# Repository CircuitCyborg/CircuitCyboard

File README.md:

# CircuitCyboard
A repo for my 153% Split Keyboard Design

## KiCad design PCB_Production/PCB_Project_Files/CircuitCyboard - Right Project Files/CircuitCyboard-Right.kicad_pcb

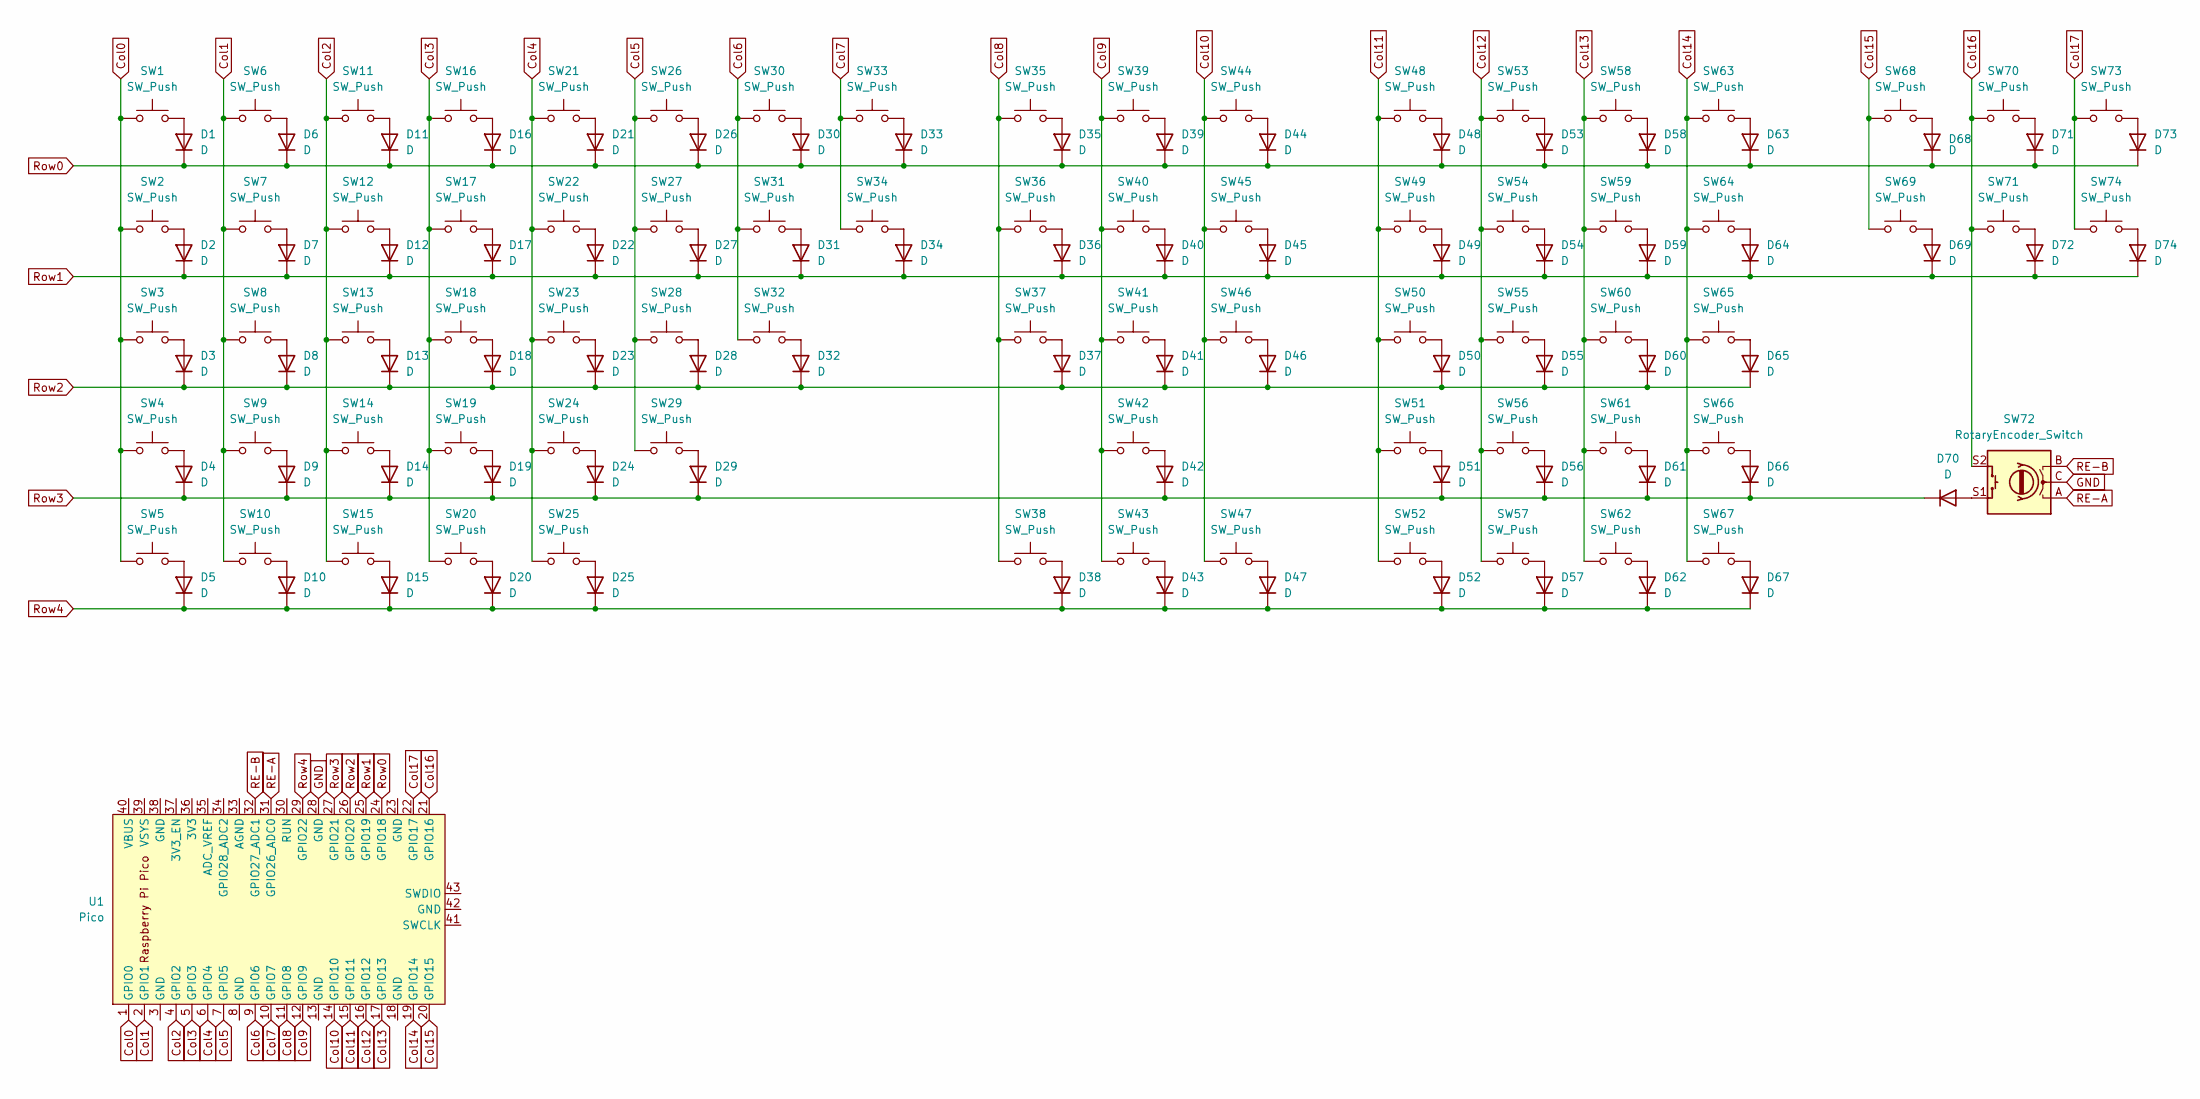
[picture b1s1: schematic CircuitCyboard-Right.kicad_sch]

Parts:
D1, D2, D3, D4, D5, D6, D7, D8, D9, D10, D11, D12, D13, D14, D15, D16, D17, D18, D19, D20, D21, D22, D23, D24, D25, D26, D27, D28, D29, D30, D31, D32, D33, D34, D35, D36, D37, D38, D39, D40, D41, D42, D43, D44, D45, D46, D47, D48, D49, D50, D51, D52, D53, D54, D55, D56, D57, D58, D59, D60, D61, D62, D63, D64, D65, D66, D67, D68, D69, D70, D71, D72, D73, D74: D; D_DO-35_SOD27_P12.70mm_Horizontal
SW1, SW2, SW3, SW4, SW6, SW7, SW8, SW9, SW10, SW11, SW12, SW13, SW14, SW15, SW16, SW17, SW18, SW19, SW20, SW21, SW22, SW23, SW24, SW25, SW26, SW27, SW28, SW30, SW31, SW34, SW35, SW36, SW37, SW38, SW39, SW40, SW41, SW42, SW43, SW44, SW45, SW46, SW47, SW48, SW49, SW50, SW51, SW52, SW53, SW54, SW55, SW56, SW57, SW58, SW59, SW60, SW61, SW62, SW63, SW64, SW65, SW66, SW67, SW68, SW69, SW70, SW71, SW73, SW74: SW_Push; SW_Cherry_MX_1.00u_PCB
SW5, SW29, SW32, SW33: SW_Push; SW_Cherry_MX_2.00u_PCB
SW72: RotaryEncoder_Switch; RotaryEncoder_Alps_EC11E-Switch_Vertical_H20mm
U1: Pico; RPi_Pico_SMD_TH

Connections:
Col0: SW1.1, SW2.1, SW3.1, SW4.1, SW5.1, U1.1 (GPIO0)
Col1: SW6.1, SW7.1, SW8.1, SW9.1, SW10.1, U1.2 (GPIO1)
Col2: SW11.1, SW12.1, SW13.1, SW14.1, SW15.1, U1.4 (GPIO2)
Col3: SW16.1, SW17.1, SW18.1, SW19.1, SW20.1, U1.5 (GPIO3)
Col4: SW21.1, SW22.1, SW23.1, SW24.1, SW25.1, U1.6 (GPIO4)
Col5: SW26.1, SW27.1, SW28.1, SW29.1, U1.7 (GPIO5)
Col6: SW30.1, SW31.1, SW32.1, U1.9 (GPIO6)
Col7: SW33.1, SW34.1, U1.10 (GPIO7)
Col8: SW35.1, SW36.1, SW37.1, SW38.1, U1.11 (GPIO8)
Col9: SW39.1, SW40.1, SW41.1, SW42.1, SW43.1, U1.12 (GPIO9)
Col10: SW44.1, SW45.1, SW46.1, SW47.1, U1.14 (GPIO10)
Col11: SW48.1, SW49.1, SW50.1, SW51.1, SW52.1, U1.15 (GPIO11)
Col12: SW53.1, SW54.1, SW55.1, SW56.1, SW57.1, U1.16 (GPIO12)
Col13: SW58.1, SW59.1, SW60.1, SW61.1, SW62.1, U1.17 (GPIO13)
Col14: SW63.1, SW64.1, SW65.1, SW66.1, SW67.1, U1.19 (GPIO14)
Col15: SW68.1, SW69.1, U1.20 (GPIO15)
Col16: SW70.1, SW71.1, SW72.S2, U1.21 (GPIO16)
Col17: SW73.1, SW74.1, U1.22 (GPIO17)
GND: SW72.C, U1.28 (GND)
unnamed: D1.2 (A), SW1.2
unnamed: D2.2 (A), SW2.2
unnamed: D3.2 (A), SW3.2
unnamed: D4.2 (A), SW4.2
unnamed: D5.2 (A), SW5.2
unnamed: D6.2 (A), SW6.2
unnamed: D7.2 (A), SW7.2
unnamed: D8.2 (A), SW8.2
unnamed: D9.2 (A), SW9.2
unnamed: D10.2 (A), SW10.2
unnamed: D11.2 (A), SW11.2
unnamed: D12.2 (A), SW12.2
unnamed: D13.2 (A), SW13.2
unnamed: D14.2 (A), SW14.2
unnamed: D15.2 (A), SW15.2
unnamed: D16.2 (A), SW16.2
unnamed: D17.2 (A), SW17.2
unnamed: D18.2 (A), SW18.2
unnamed: D19.2 (A), SW19.2
unnamed: D20.2 (A), SW20.2
unnamed: D21.2 (A), SW21.2
unnamed: D22.2 (A), SW22.2
unnamed: D23.2 (A), SW23.2
unnamed: D24.2 (A), SW24.2
unnamed: D25.2 (A), SW25.2
unnamed: D26.2 (A), SW26.2
unnamed: D27.2 (A), SW27.2
unnamed: D28.2 (A), SW28.2
unnamed: D29.2 (A), SW29.2
unnamed: D30.2 (A), SW30.2
unnamed: D31.2 (A), SW31.2
unnamed: D32.2 (A), SW32.2
unnamed: D33.2 (A), SW33.2
unnamed: D34.2 (A), SW34.2
unnamed: D35.2 (A), SW35.2
unnamed: D36.2 (A), SW36.2
unnamed: D37.2 (A), SW37.2
unnamed: D38.2 (A), SW38.2
unnamed: D39.2 (A), SW39.2
unnamed: D40.2 (A), SW40.2
unnamed: D41.2 (A), SW41.2
unnamed: D42.2 (A), SW42.2
unnamed: D43.2 (A), SW43.2
unnamed: D44.2 (A), SW44.2
unnamed: D45.2 (A), SW45.2
unnamed: D46.2 (A), SW46.2
unnamed: D47.2 (A), SW47.2
unnamed: D48.2 (A), SW48.2
unnamed: D49.2 (A), SW49.2
unnamed: D50.2 (A), SW50.2
unnamed: D51.2 (A), SW51.2
unnamed: D52.2 (A), SW52.2
unnamed: D53.2 (A), SW53.2
unnamed: D54.2 (A), SW54.2
unnamed: D55.2 (A), SW55.2
unnamed: D56.2 (A), SW56.2
unnamed: D57.2 (A), SW57.2
unnamed: D58.2 (A), SW58.2
unnamed: D59.2 (A), SW59.2
unnamed: D60.2 (A), SW60.2
unnamed: D61.2 (A), SW61.2
unnamed: D62.2 (A), SW62.2
unnamed: D63.2 (A), SW63.2
unnamed: D64.2 (A), SW64.2
unnamed: D65.2 (A), SW65.2
unnamed: D66.2 (A), SW66.2
unnamed: D67.2 (A), SW67.2
unnamed: D68.2 (A), SW68.2
unnamed: D69.2 (A), SW69.2
unnamed: D70.2 (A), SW72.S1
unnamed: D71.2 (A), SW70.2
unnamed: D72.2 (A), SW71.2
unnamed: D73.2 (A), SW73.2
unnamed: D74.2 (A), SW74.2
RE-A: SW72.A, U1.31 (GPIO26_ADC0)
RE-B: SW72.B, U1.32 (GPIO27_ADC1)
Row0: D1.1 (K), D6.1 (K), D11.1 (K), D16.1 (K), D21.1 (K), D26.1 (K), D30.1 (K), D33.1 (K), D35.1 (K), D39.1 (K), D44.1 (K), D48.1 (K), D53.1 (K), D58.1 (K), D63.1 (K), D68.1 (K), D71.1 (K), D73.1 (K), U1.24 (GPIO18)
Row1: D2.1 (K), D7.1 (K), D12.1 (K), D17.1 (K), D22.1 (K), D27.1 (K), D31.1 (K), D34.1 (K), D36.1 (K), D40.1 (K), D45.1 (K), D49.1 (K), D54.1 (K), D59.1 (K), D64.1 (K), D69.1 (K), D72.1 (K), D74.1 (K), U1.25 (GPIO19)
Row2: D3.1 (K), D8.1 (K), D13.1 (K), D18.1 (K), D23.1 (K), D28.1 (K), D32.1 (K), D37.1 (K), D41.1 (K), D46.1 (K), D50.1 (K), D55.1 (K), D60.1 (K), D65.1 (K), U1.26 (GPIO20)
Row3: D4.1 (K), D9.1 (K), D14.1 (K), D19.1 (K), D24.1 (K), D29.1 (K), D42.1 (K), D51.1 (K), D56.1 (K), D61.1 (K), D66.1 (K), D70.1 (K), U1.27 (GPIO21)
Row4: D5.1 (K), D10.1 (K), D15.1 (K), D20.1 (K), D25.1 (K), D38.1 (K), D43.1 (K), D47.1 (K), D52.1 (K), D57.1 (K), D62.1 (K), D67.1 (K), U1.29 (GPIO22)

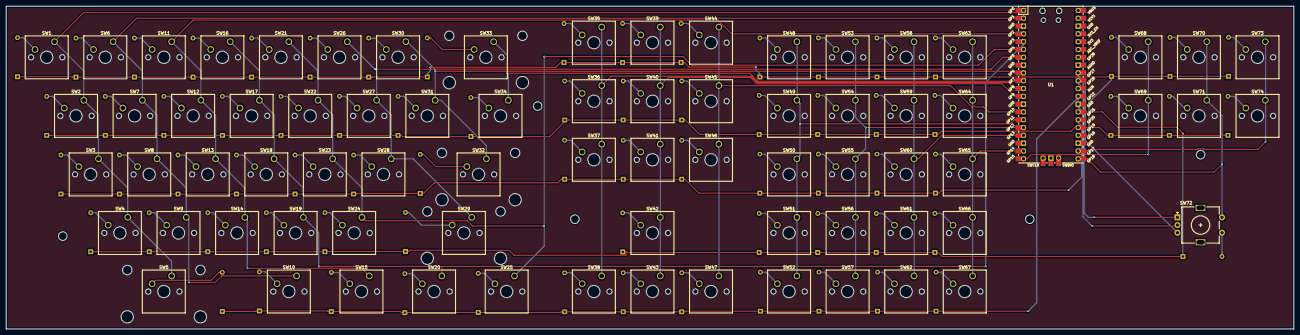
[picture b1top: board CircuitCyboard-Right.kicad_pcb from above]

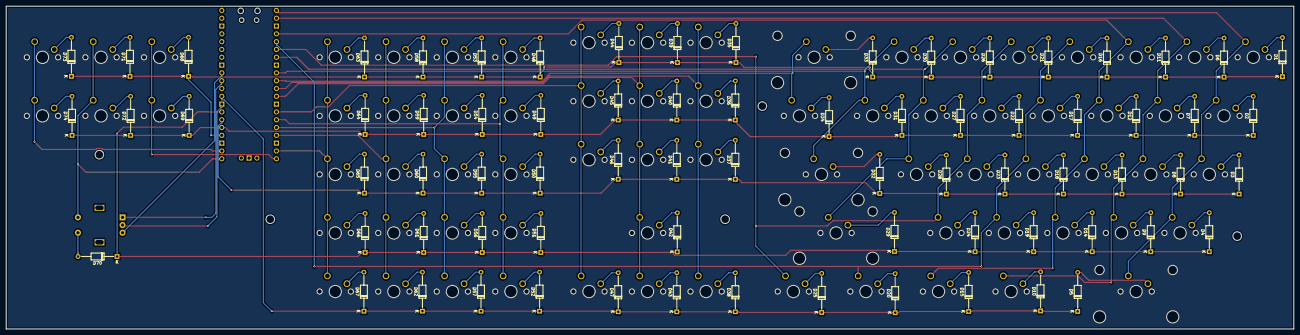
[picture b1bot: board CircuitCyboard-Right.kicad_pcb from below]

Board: 2 copper layers, 418.9 x 105.0 mm, 149 parts (74 on the bottom side), 100 nets.

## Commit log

2025-06-10 Create Firmware
2025-06-10 Rename Firmware.ReadMe.md to readme.md
2025-10-09 Add files via upload
    Final BOM
2025-10-09 Delete BOM.CircuitCyboard_Final.csv
    Delete Original BOM
2025-10-09 Update readme.md
    Upload Rendering of Final Board
2025-10-09 Add files via upload
    Add PCB Project Files
2025-10-09 Uploading knob and board with knob renderings
2025-10-09 Rename Main Knob.zip to Main Knob STEP.zip
2025-10-09 Update readme.md
    Add link to the public Onshape Document
2025-10-16 Update BOM with new part details and links
    More correction/changes in a second
2025-10-16 Update BOM with new pricing
2025-10-16 Update BOM with new part details and links
2025-10-16 Update BOM with new parts and pricing details
2025-10-16 Update BOM with additional components and links
2025-10-16 add updated BOM
2026-02-24 Updated images in Renderings.md
    Replaced old screenshot links with new image tags for better formatting.
2026-02-24 Create Left
2026-02-24 Create File
2026-02-24 Update Left Case Files
2026-02-24 Create Space
2026-02-24 Update README with latest project details and images
2026-02-24 Update readme with project details and latest changes
2026-02-26 Update BOM with Correct links
2026-03-06 Update BOM with correct/current pricing
2026-03-15 Update BOM with new pricing and supplier links
